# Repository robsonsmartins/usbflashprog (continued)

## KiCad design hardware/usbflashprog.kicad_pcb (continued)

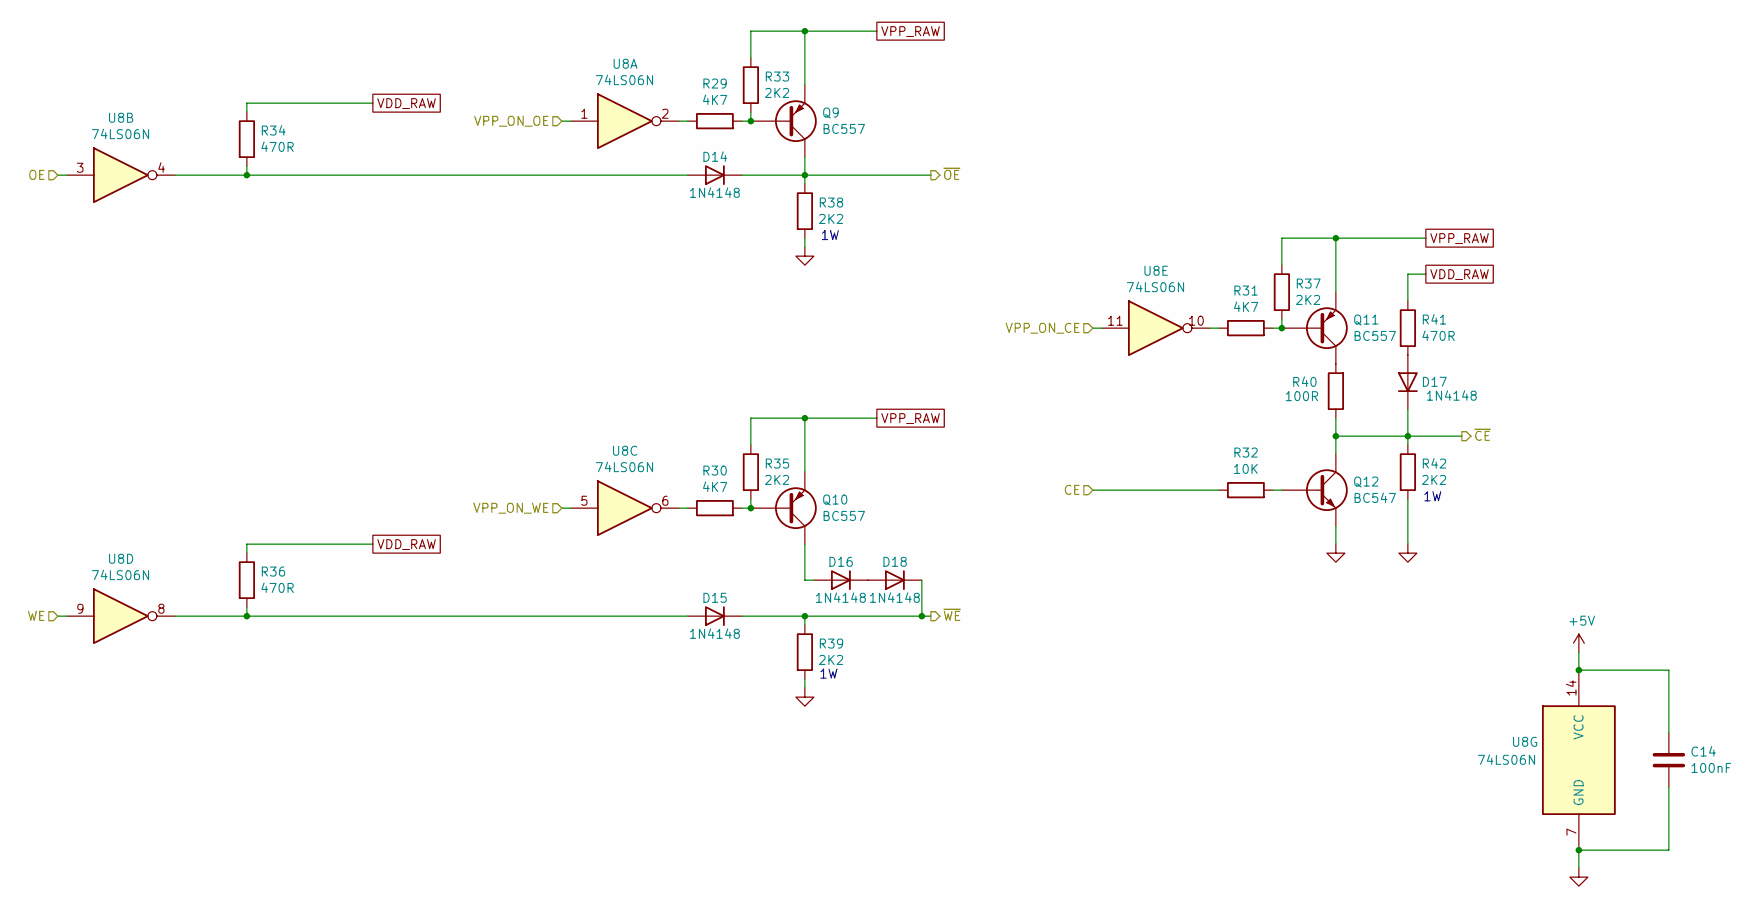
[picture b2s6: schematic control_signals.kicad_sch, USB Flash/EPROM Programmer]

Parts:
C14: 100nF; C_Disc_D5.0mm_W2.5mm_P5.00mm
D14, D15, D16, D17, D18: 1N4148; D_DO-34_SOD68_P7.62mm_Horizontal
Q9, Q10, Q11: BC557; TO-92_Inline_Wide
Q12: BC547; TO-92_Inline_Wide
R29, R30, R31: 4K7; R_Axial_DIN0204_L3.6mm_D1.6mm_P7.62mm_Horizontal
R32: 10K; R_Axial_DIN0204_L3.6mm_D1.6mm_P7.62mm_Horizontal
R33, R35, R37, R38, R39, R42: 2K2; R_Axial_DIN0204_L3.6mm_D1.6mm_P7.62mm_Horizontal
R34, R36, R41: 470R; R_Axial_DIN0204_L3.6mm_D1.6mm_P7.62mm_Horizontal
R40: 100R; R_Axial_DIN0204_L3.6mm_D1.6mm_P7.62mm_Horizontal
U8: 74LS06N; DIP-14_W7.62mm

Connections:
+5V: C14.1, U8.14 (VCC); also elsewhere on the board
/CPU/CE: R32.1; also elsewhere on the board
/CPU/OE: U8.3; also elsewhere on the board
/CPU/VPP_ON_CE: U8.11; also elsewhere on the board
/CPU/VPP_ON_OE: U8.1; also elsewhere on the board
/CPU/VPP_ON_WE: U8.5; also elsewhere on the board
/CPU/WE: U8.9; also elsewhere on the board
/~CE: D17.1 (K), Q12.1 (C), R40.1, R42.1; also elsewhere on the board
/~OE: D14.1 (K), Q9.1 (C), R38.1; also elsewhere on the board
/~WE: D15.1 (K), D18.1 (K), R39.1; also elsewhere on the board
GND: C14.2, Q12.3 (E), R38.2, R39.2, R42.2, U8.7 (GND); also elsewhere on the board
unnamed: D14.2 (A), R34.2, U8.4
unnamed: D15.2 (A), R36.2, U8.8
unnamed: D16.2 (A), Q10.1 (C)
unnamed: D16.1 (K), D18.2 (A)
unnamed: D17.2 (A), R41.2
unnamed: Q9.2 (B), R29.2, R33.2
unnamed: Q10.2 (B), R30.2, R35.2
unnamed: Q11.2 (B), R31.2, R37.2
unnamed: Q11.1 (C), R40.2
unnamed: Q12.2 (B), R32.2
unnamed: R29.1, U8.2
unnamed: R30.1, U8.6
unnamed: R31.1, U8.10
VDD_RAW: R34.1, R36.1, R41.1; also elsewhere on the board
VPP_RAW: Q9.3 (E), Q10.3 (E), Q11.3 (E), R33.1, R35.1, R37.1; also elsewhere on the board

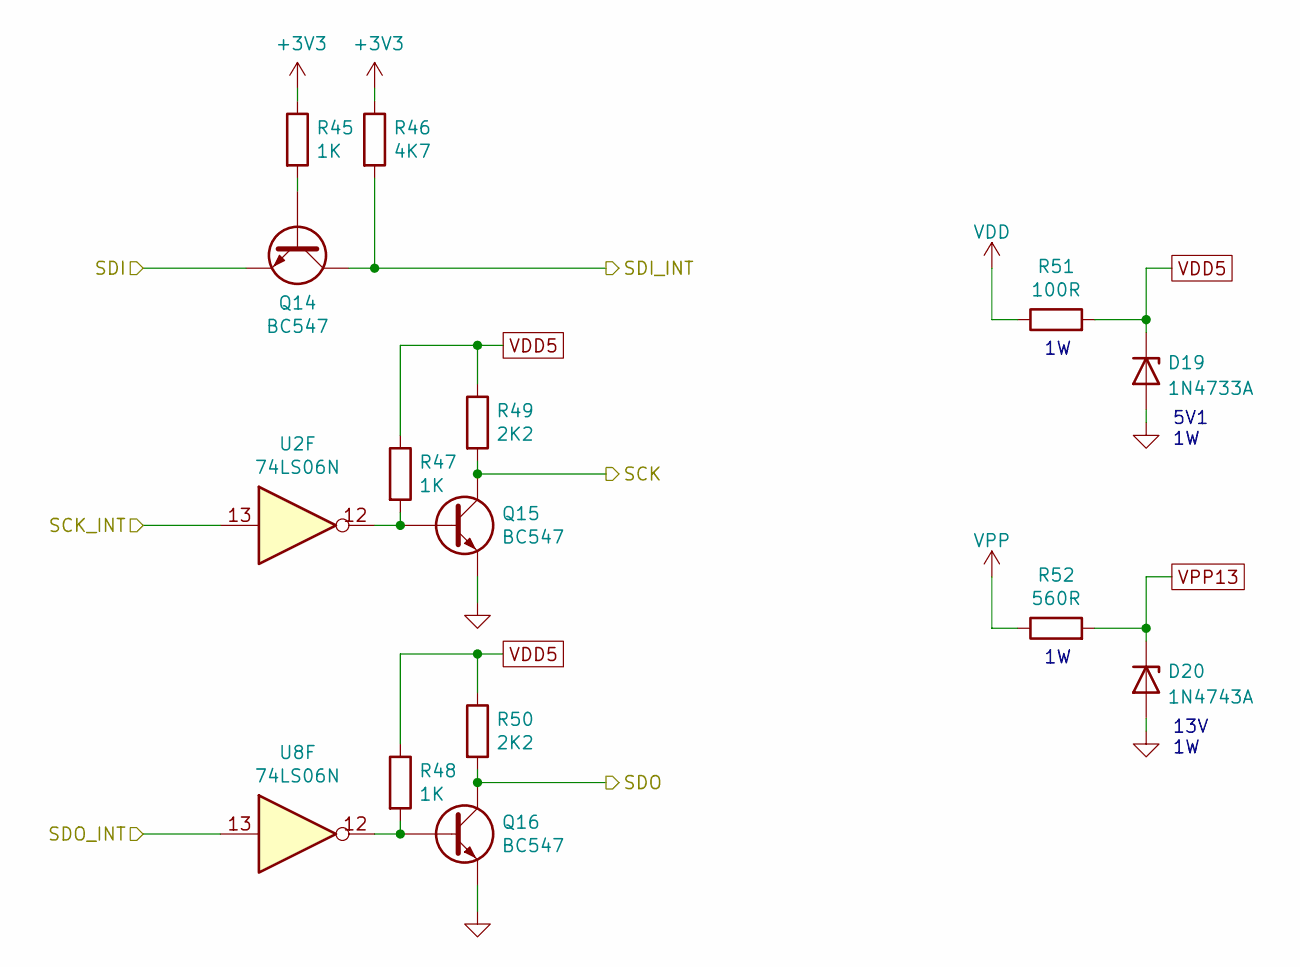
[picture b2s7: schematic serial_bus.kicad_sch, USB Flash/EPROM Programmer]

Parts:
D19: 1N4733A; D_DO-35_SOD27_P7.62mm_Horizontal
D20: 1N4743A; D_DO-35_SOD27_P7.62mm_Horizontal
Q14, Q15, Q16: BC547; TO-92_Inline_Wide
R45, R47, R48: 1K; R_Axial_DIN0204_L3.6mm_D1.6mm_P7.62mm_Horizontal
R46: 4K7; R_Axial_DIN0204_L3.6mm_D1.6mm_P7.62mm_Horizontal
R49, R50: 2K2; R_Axial_DIN0204_L3.6mm_D1.6mm_P7.62mm_Horizontal
R51: 100R; R_Axial_DIN0204_L3.6mm_D1.6mm_P7.62mm_Horizontal
R52: 560R; R_Axial_DIN0207_L6.3mm_D2.5mm_P10.16mm_Horizontal
U2, U8: 74LS06N; DIP-14_W7.62mm

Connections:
+3V3: R45.1, R46.1; also elsewhere on the board
/CPU/SCK_INT: U2.13; also elsewhere on the board
/CPU/SDI_INT: Q14.1 (C), R46.2; also elsewhere on the board
/CPU/SDO_INT: U8.13; also elsewhere on the board
/SCK: Q15.1 (C), R49.2; also elsewhere on the board
/SDI: Q14.3 (E); also elsewhere on the board
/SDO: Q16.1 (C), R50.2; also elsewhere on the board
GND: D19.2 (A), D20.2 (A), Q15.3 (E), Q16.3 (E); also elsewhere on the board
unnamed: Q14.2 (B), R45.2
unnamed: Q15.2 (B), R47.2, U2.12
unnamed: Q16.2 (B), R48.2, U8.12
VDD: R51.1; also elsewhere on the board
VDD5: D19.1 (K), R47.1, R48.1, R49.1, R50.1, R51.2; also elsewhere on the board
VPP: R52.1; also elsewhere on the board
VPP13: D20.1 (K), R52.2; also elsewhere on the board

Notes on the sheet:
13V 1W
5V1 1W

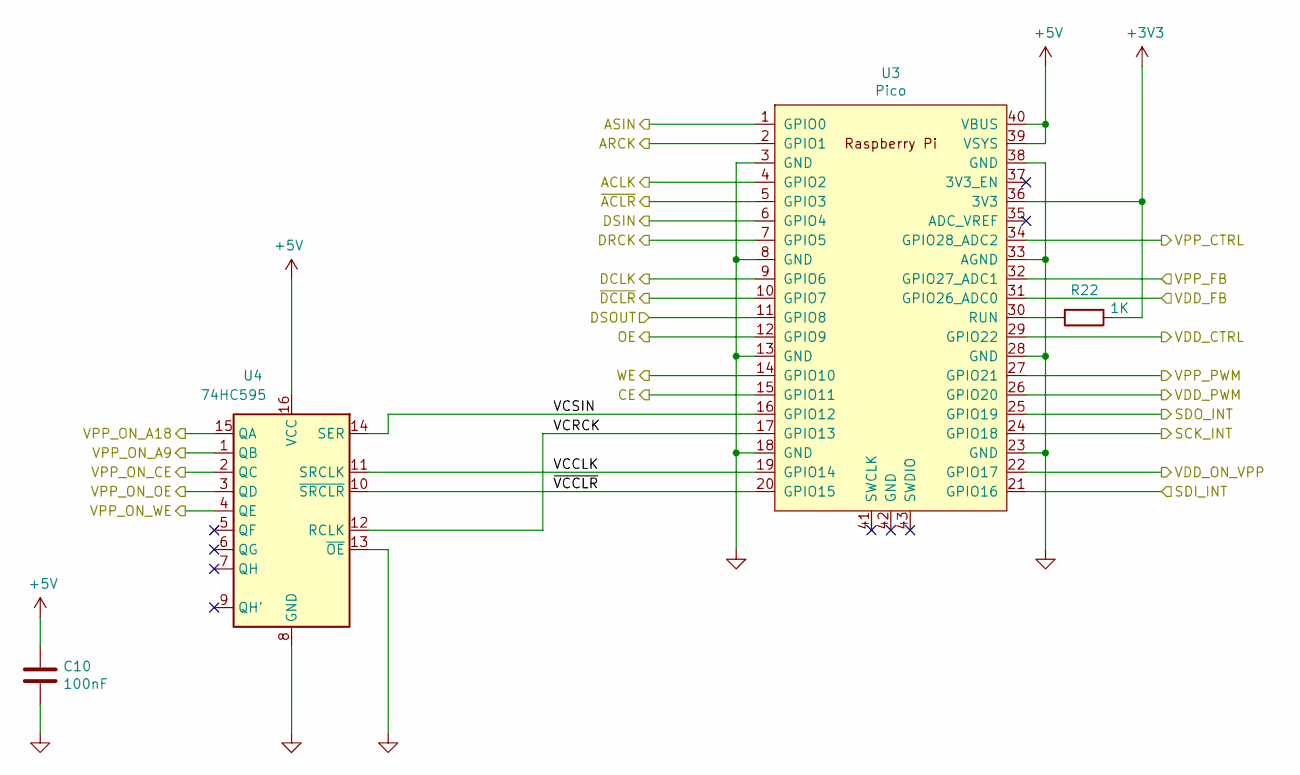
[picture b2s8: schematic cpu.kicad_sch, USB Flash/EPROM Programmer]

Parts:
C10: 100nF; C_Disc_D5.0mm_W2.5mm_P5.00mm
R22: 1K; R_Axial_DIN0204_L3.6mm_D1.6mm_P7.62mm_Horizontal
U3: Pico; RPi_Pico_SMD_TH
U4: 74HC595; DIP-16_W7.62mm

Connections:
+3V3: R22.1, U3.36 (3V3); also elsewhere on the board
+5V: C10.1, U3.39 (VSYS), U3.40 (VBUS), U4.16 (VCC); also elsewhere on the board
/Address Bus/ACLK: U3.4 (GPIO2); also elsewhere on the board
/Address Bus/ARCK: U3.2 (GPIO1); also elsewhere on the board
/Address Bus/ASIN: U3.1 (GPIO0); also elsewhere on the board
/Address Bus/VPP_ON_A9: U4.1 (QB); also elsewhere on the board
/Address Bus/VPP_ON_A18: U4.15 (QA); also elsewhere on the board
/Address Bus/~ACLR: U3.5 (GPIO3); also elsewhere on the board
/CPU/CE: U3.15 (GPIO11); also elsewhere on the board
/CPU/DCLK: U3.9 (GPIO6); also elsewhere on the board
/CPU/DRCK: U3.7 (GPIO5); also elsewhere on the board
/CPU/DSIN: U3.6 (GPIO4); also elsewhere on the board
/CPU/DSOUT: U3.11 (GPIO8); also elsewhere on the board
/CPU/OE: U3.12 (GPIO9); also elsewhere on the board
/CPU/SCK_INT: U3.24 (GPIO18); also elsewhere on the board
/CPU/SDI_INT: U3.21 (GPIO16); also elsewhere on the board
/CPU/SDO_INT: U3.25 (GPIO19); also elsewhere on the board
/CPU/VCCLK: U3.19 (GPIO14), U4.11 (SRCLK)
/CPU/VCRCK: U3.17 (GPIO13), U4.12 (RCLK)
/CPU/VCSIN: U3.16 (GPIO12), U4.14 (SER)
/CPU/VDD_CTRL: U3.29 (GPIO22); also elsewhere on the board
/CPU/VDD_FB: U3.31 (GPIO26_ADC0); also elsewhere on the board
/CPU/VDD_ON_VPP: U3.22 (GPIO17); also elsewhere on the board
/CPU/VDD_PWM: U3.26 (GPIO20); also elsewhere on the board
/CPU/VPP_CTRL: U3.34 (GPIO28_ADC2); also elsewhere on the board
/CPU/VPP_FB: U3.32 (GPIO27_ADC1); also elsewhere on the board
/CPU/VPP_ON_CE: U4.2 (QC); also elsewhere on the board
/CPU/VPP_ON_OE: U4.3 (QD); also elsewhere on the board
/CPU/VPP_ON_WE: U4.4 (QE); also elsewhere on the board
/CPU/VPP_PWM: U3.27 (GPIO21); also elsewhere on the board
/CPU/WE: U3.14 (GPIO10); also elsewhere on the board
/CPU/~DCLR: U3.10 (GPIO7); also elsewhere on the board
/CPU/~VCCLR: U3.20 (GPIO15), U4.10 (~SRCLR)
GND: C10.2, U3.3 (GND), U3.8 (GND), U3.13 (GND), U3.18 (GND), U3.23 (GND), U3.28 (GND), U3.33 (AGND), U3.38 (GND), U4.8 (GND), U4.13 (~OE); also elsewhere on the board
unnamed: R22.2, U3.30 (RUN)

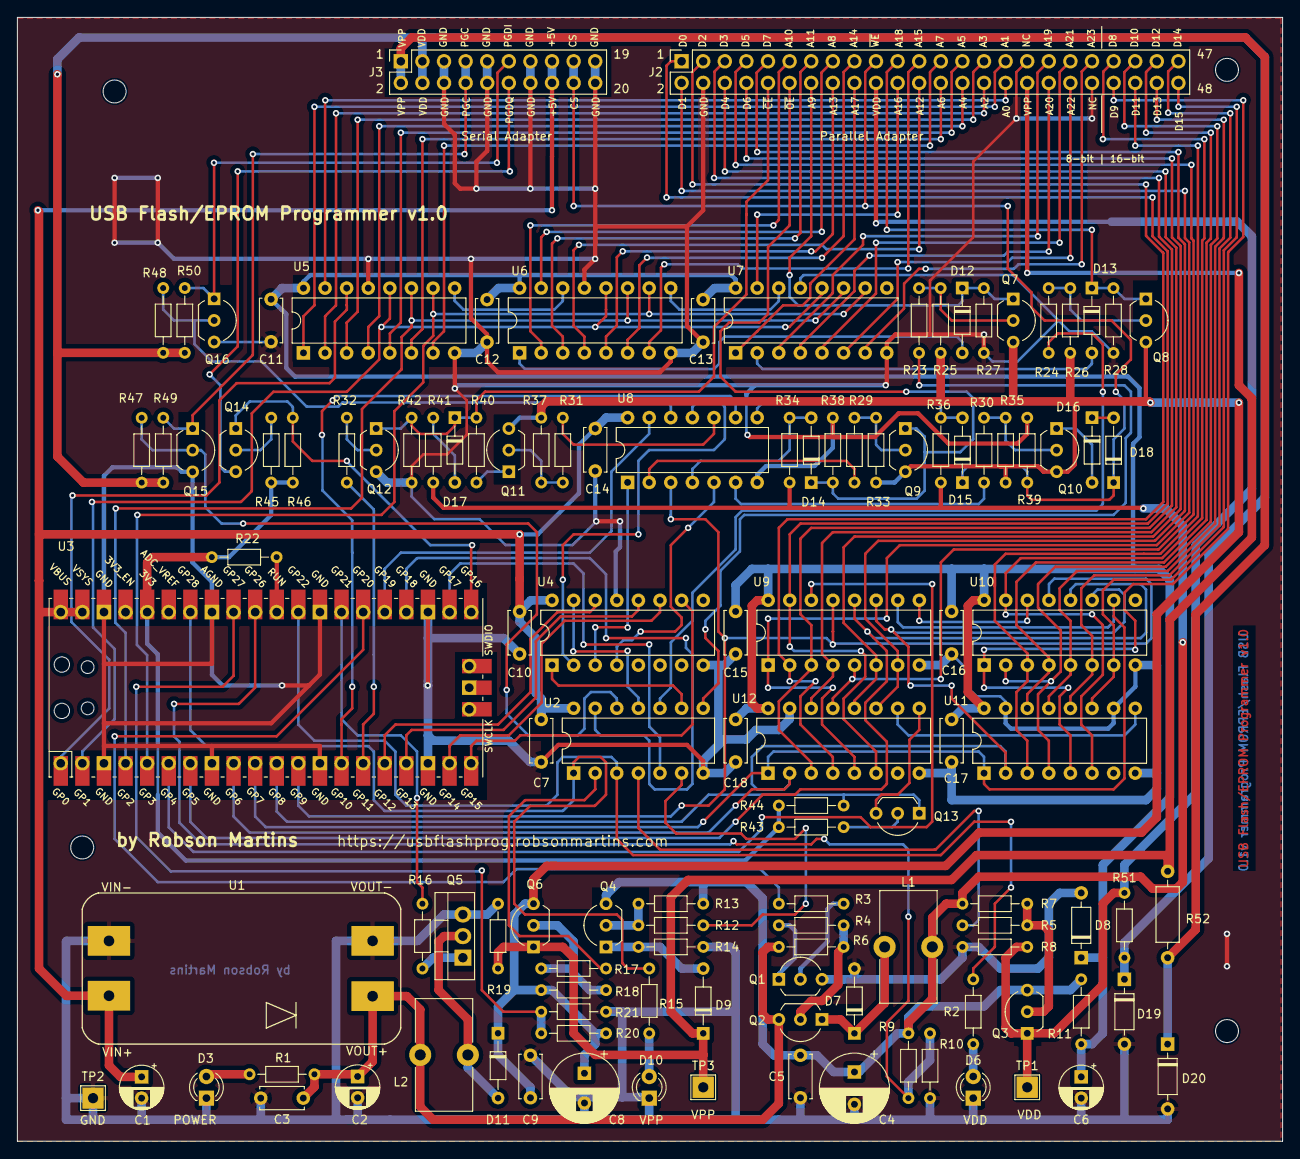
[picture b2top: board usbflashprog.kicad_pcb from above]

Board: 2 copper layers, 148.8 x 132.2 mm, 121 parts (0 on the bottom side), 133 nets.

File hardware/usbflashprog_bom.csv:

"Source:","E:\Users\Robson\Documentos\github-projects\usbflashprog\hardware\usbflashprog.kicad_sch"
"Date:","14/11/2023 17:15:45"
"Tool:","Eeschema 7.0.5"
"Generator:","C:\Program Files\KiCad\bin\scripting\plugins/bom_csv_grouped_by_value.py"
"Component Count:","121"

"Collated Components:"

"Item","Qty","Reference(s)","Value","LibPart","Footprint","Datasheet","DNP"
"1","2","C1, C2","10uF","Device:C_Polarized","Capacitor_THT:CP_Radial_D5.0mm_P2.50mm","~",""
"2","13","C3, C5, C7, C9, C10, C11, C12, C13, C14, C15, C16, C17, C18","100nF","Device:C","Capacitor_THT:C_Disc_D6.0mm_W2.5mm_P5.00mm","~",""
"3","1","C4","470uF","Device:C_Polarized","Capacitor_THT:CP_Radial_D8.0mm_P3.80mm","~",""
"4","1","C6","22uF","Device:C_Polarized","Capacitor_THT:CP_Radial_D5.0mm_P2.50mm","~",""
"5","1","C8","100uF","Device:C_Polarized","Capacitor_THT:CP_Radial_D8.0mm_P3.50mm","~",""
"6","1","D3","GREEN","Device:LED","LED_THT:LED_D3.0mm","~",""
"7","1","D6","RED","Device:LED","LED_THT:LED_D3.0mm","~",""
"8","2","D7, D11","BAT46","Diode:BAT46","Diode_THT:D_DO-35_SOD27_P7.62mm_Horizontal","http://www.vishay.com/docs/85662/bat46.pdf",""
"9","2","D8, D19","1N4733A","Diode:1N47xxA","Diode_THT:D_DO-41_SOD81_P10.16mm_Horizontal","https://www.vishay.com/docs/85816/1n4728a.pdf",""
"10","8","D9, D12, D13, D14, D15, D16, D17, D18","1N4148","Diode:1N4148","Diode_THT:D_DO-35_SOD27_P7.62mm_Horizontal","https://assets.nexperia.com/documents/data-sheet/1N4148_1N4448.pdf",""
"11","1","D10","YELLOW","Device:LED","LED_THT:LED_D3.0mm","~",""
"12","1","D20","1N4743A","Diode:1N47xxA","Diode_THT:D_DO-41_SOD81_P10.16mm_Horizontal","https://www.vishay.com/docs/85816/1n4728a.pdf",""
"13","1","J2","Parallel Adapter","Connector_Generic:Conn_02x24_Odd_Even","Connector_PinSocket_2.54mm:PinSocket_2x24_P2.54mm_Vertical","~",""
"14","1","J3","Serial Adapter","Connector_Generic:Conn_02x10_Odd_Even","Connector_PinSocket_2.54mm:PinSocket_2x10_P2.54mm_Vertical","~",""
"15","1","L1","100uH","Device:L_Ferrite","Inductor_THT:L_Toroid_Vertical_L13.0mm_W6.5mm_P5.60mm","~",""
"16","1","L2","300uH","Device:L_Ferrite","Inductor_THT:L_Toroid_Vertical_L13.0mm_W6.5mm_P5.60mm","~",""
"17","4","Q1, Q12, Q13, Q16","BC547","Transistor_BJT:BC547","Package_TO_SOT_THT:TO-92_Inline_Wide","https://www.onsemi.com/pub/Collateral/BC550-D.pdf",""
"18","1","Q2","BC327",":BC327_1","Package_TO_SOT_THT:TO-92_Inline_Wide","http://www.onsemi.com/pub_link/Collateral/BC327-D.PDF",""
"19","1","Q3","BC327",":BC327_2","Package_TO_SOT_THT:TO-92_Inline_Wide","http://www.onsemi.com/pub_link/Collateral/BC327-D.PDF",""
"20","2","Q4, Q6","BC327","Transistor_BJT:BC327","Package_TO_SOT_THT:TO-92_Inline_Wide","http://www.onsemi.com/pub_link/Collateral/BC327-D.PDF",""
"21","1","Q5","TIP120","Transistor_BJT:TIP120","Package_TO_SOT_THT:TO-220-3_Vertical","https://www.onsemi.com/pub/Collateral/TIP120-D.PDF",""
"22","2","Q7, Q9","BC557",":BC557_1","Package_TO_SOT_THT:TO-92_Inline_Wide","https://www.onsemi.com/pub/Collateral/BC556BTA-D.pdf",""
"23","2","Q8, Q11","BC557","Transistor_BJT:BC557","Package_TO_SOT_THT:TO-92_Inline_Wide","https://www.onsemi.com/pub/Collateral/BC556BTA-D.pdf",""
"24","1","Q10","BC557",":BC557_2","Package_TO_SOT_THT:TO-92_Inline_Wide","https://www.onsemi.com/pub/Collateral/BC556BTA-D.pdf",""
"25","1","Q14","BC547",":BC547_1","Package_TO_SOT_THT:TO-92_Inline_Wide","https://www.onsemi.com/pub/Collateral/BC550-D.pdf",""
"26","1","Q15","BC547",":BC547_2","Package_TO_SOT_THT:TO-92_Inline_Wide","https://www.onsemi.com/pub/Collateral/BC550-D.pdf",""
"27","19","R1, R5, R6, R7, R12, R13, R18, R25, R26, R27, R28, R33, R35, R37, R38, R39, R42, R49, R50","2K2","Device:R","Resistor_THT:R_Axial_DIN0207_L6.3mm_D2.5mm_P10.16mm_Horizontal","~",""
"28","5","R2, R11, R15, R40, R51","100R","Device:R","Resistor_THT:R_Axial_DIN0207_L6.3mm_D2.5mm_P10.16mm_Horizontal","~",""
"29","7","R3, R8, R22, R43, R45, R47, R48","1K","Device:R","Resistor_THT:R_Axial_DIN0207_L6.3mm_D2.5mm_P10.16mm_Horizontal","~",""
"30","10","R4, R17, R19, R23, R24, R29, R30, R31, R44, R46","4K7","Device:R","Resistor_THT:R_Axial_DIN0207_L6.3mm_D2.5mm_P10.16mm_Horizontal","~",""
"31","5","R9, R21, R34, R36, R41","470R","Device:R","Resistor_THT:R_Axial_DIN0207_L6.3mm_D2.5mm_P10.16mm_Horizontal","~",""
"32","1","R10","330R","Device:R","Resistor_THT:R_Axial_DIN0207_L6.3mm_D2.5mm_P10.16mm_Horizontal","~",""
"33","2","R14, R32","10K","Device:R","Resistor_THT:R_Axial_DIN0207_L6.3mm_D2.5mm_P10.16mm_Horizontal","~",""
"34","1","R16","220R","Device:R","Resistor_THT:R_Axial_DIN0207_L6.3mm_D2.5mm_P10.16mm_Horizontal","~",""
"35","1","R20","3K9","Device:R","Resistor_THT:R_Axial_DIN0207_L6.3mm_D2.5mm_P10.16mm_Horizontal","~",""
"36","1","R52","560R","Device:R","Resistor_THT:R_Axial_DIN0309_L9.0mm_D3.2mm_P15.24mm_Horizontal","~",""
"37","1","TP1","VDD","Connector:TestPoint","TestPoint:TestPoint_THTPad_2.5x2.5mm_Drill1.2mm","~",""
"38","1","TP2","GND","Connector:TestPoint","TestPoint:TestPoint_THTPad_2.5x2.5mm_Drill1.2mm","~",""
"39","1","TP3","VPP","Connector:TestPoint","TestPoint:TestPoint_THTPad_2.5x2.5mm_Drill1.2mm","~",""
"40","1","U1","MT3608 Module","DC2DC_Modules:MT3608_Module","DC2DC_Modules:MT3608_module","https://support.envistiamall.com/kb/mt3608-2v-28v-micro-usb-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",""
"41","2","U2, U8","74LS06N","74xx:74LS06N","Package_DIP:DIP-14_W7.62mm","http://www.ti.com/lit/gpn/sn74LS06N",""
"42","1","U3","Pico","MCU_RaspberryPi_and_Boards:Pico","MCU_RaspberryPi_and_Boards:RPi_Pico_SMD_TH","",""
"43","6","U4, U5, U6, U7, U9, U10","74HC595","74xx:74HC595","Package_DIP:DIP-16_W7.62mm","http://www.ti.com/lit/ds/symlink/sn74hc595.pdf",""
"44","2","U11, U12","74HC165","74xx:74HC165","Package_DIP:DIP-16_W7.62mm","https://assets.nexperia.com/documents/data-sheet/74HC_HCT165.pdf",""

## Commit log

2022-04-19 Initial commit (migrated from sourceforge.net).
2022-04-23 Rev.E. CPU changed to Raspberry Pi Pico. Updated diagrams. Removed PT_BR translation.
2022-04-25 Rev.E. Updated project site.
2022-04-25 Rev.E. Initial hardware design.
2022-04-26 Rev.E. Update Readme. Add LibreOffice lock files to gitignore.
2022-04-27 Rev.E. Updated hardware design.
2022-04-27 Rev.E. Add readme to doc directory.
2022-04-28 Rev.E. Updated specifications document and hardware design.
2022-04-28 Rev.E. Updated readme and hardware BOM.
2022-04-30 Rev.E. Updated R51 wattage.
2022-05-03 Rev.E. Add Initial Firmware Project and documentation.
2022-05-03 Rev.E. Created github-pages documentation
2022-05-04 Rev.E. Created github-pages documentation.
2022-05-04 Rev.E. Updated documentation.
2022-05-04 Rev.E. Update readme.
2022-05-04 Rev.E. Update index.md
2022-05-04 Rev.E. Added UT's for firmware project.
2022-05-07 Rev.E. Add ADC class and UT.
2022-05-08 Rev.E. Updated documentation. Added code coverage report.
2022-05-08 Rev.E. Updated cmake scripts. Updated documentation.
2022-05-08 Rev.E. Updated CI/CD script.
2022-05-08 Rev.E. Updated pulse time test tolerance.
2022-05-08 Rev.E. Updated CI/CD code analysis.
2022-05-09 Rev.E. Created PWM Class. Updated documentation.
2022-05-09 Rev.E. Add tests for PWM Class.
2022-05-09 Rev.E. Update codeql analysis script.
2022-05-09 Rev.E. Create initial security policy file.
2022-05-10 Rev.E. Add MultiCore HAL class and UT.
2022-05-12 Rev.E. Add DC2DC circuits class and UT. Revised all code and doxygen docs.
2022-05-15 Rev.E. Add Dc2Dc Converter and Voltage Generator classes.
2022-05-16 Rev.E. Add UT for VGenerator and revised Dc2Dc, Pwm and VGenerator classes.
2022-05-16 Rev.E. Add Test Points for VDD/VPP/GND.
2022-05-19 DRAFT. Proposal with Boost Converter to eliminate external power supply.
2022-05-23 Rev.E. Add flash space class and UT. Updated VGenerator.
2022-05-25 Rev.E. Update VGenerator class and UT. Update README. Update docs.
2022-05-25 Rev.E. Update README
2022-05-25 Rev.E. Update docs
2022-05-25 Rev.E. Update VGenerator and UT.
2022-05-29 Rev.E. Add string, serial and runner classes
2022-05-29 Rev.E. Update classes
2022-05-29 Rev.E. Update documentation
2022-05-31 Rev.E. Update String, Serial and Runner classes
2022-05-31 Rev.E. Add UT's for Serial and String classes
2022-05-31 Rev.E. Update firmware documentation
2022-06-02 Rev.F. Updated schematics
2022-06-02 Rev.F. Added codes/commands for communication
2022-06-02 Rev.F. Initial software project
2022-06-02 Rev.F. Updated documentation
2022-06-02 Rev.F. Ignore backup files from Kicad.
2022-06-02 Rev.F Update CMake directives for ts compilation
2022-06-03 Rev.F. Update README. Add BUILD instructions
2022-06-03 Rev.F. Ignore backups from Kicad
2022-06-03 Rev.F. Update BUILD instructions
2022-06-05 Rev.F. Updated software project and documentation
2022-06-06 Rev.F. Updated software project
2022-06-06 Rev.F. Initial version
2022-06-06 Rev.F. Removed travis support
2022-06-08 Rev.F. Update github action scripts
2022-06-09 Rev.F. Update documentation
2022-06-09 Rev.F. Add DEB package system
2022-06-11 Rev.F. Update Firmware project
2022-06-12 Rev.F. Update Software project
2022-06-25 Rev.F. Update build scripts
2022-06-30 Rev.F. Add support to build on macos
2022-07-06 Rev.F. Update project
2022-07-07 Rev.F. Add support to Qt < 5.10
2022-07-10 Rev.F. Remove warnings
2022-07-10 Rev.F. Add support to FreeBSD
2022-07-14 Rev.F. Update GUI
2022-07-14 Rev.F. Add Unit Tests
2022-08-17 Rev.F. Add CDC driver to Windows 7
2022-08-18 Rev.F. Add basic hex editor
2022-08-24 Rev.F. Update hex editor and software project
2022-08-30 simulator: Initial commit
2022-08-30 simulator: iowrapper
2022-09-01 simulator: prog, chip, emuprog gui, install-script
2022-09-13 simulator: update emuprog gui
2022-09-15 Rev.F. Update workflow for build software
2022-09-29 Rev.F. Firmware - add data and address bus support
2022-09-29 Rev.F. Update firmware documentation
2022-09-29 Rev.F. Software - add data and address bus support
2022-09-29 Rev.F. Update software documentation
2023-10-20 Rev.F. Update software and firmware build docs
    Committer: Robson Martins <robsonsmartins@gmail.com>
2023-10-21 Rev.G. Update README
2023-11-14 Rev.G. Change external power supply to a MT3606 DC-DC Module
2023-11-17 Rev.G. Update specs
2023-11-17 Rev.G. Fix type errors in backend/opcodes
2023-11-21 Rev.G. Fix Build Software Action errors
2023-11-21 Rev.G. Fix compilation warnings under macos
2023-11-29 Rev.G. Update software backend/runner
2023-11-29 Rev.G. Update software tests
2023-12-13 simulator: fix cross dll generation under linux
2023-12-13 simulator: add the code documentation
2023-12-13 simulator: fix 32-bit executables calls
2023-12-13 simulator: add code formater
2023-12-13 Rev.G. Update software documentation
2023-12-13 Rev.G. Update software coverage, build and test scripts
2023-12-13 Rev.G. Update software coverage documentation
2023-12-13 Rev.G. Update firmware documentation
2023-12-13 Rev.G. Update firmware coverage documentation
2023-12-13 Rev.G. Update firmware coverage, build and test scripts
2023-12-13 Rev.G. Update software source format. Add base device and actions. Update ui.
2023-12-13 Rev.G. Fix cmake 3.0 deprecation in third party
2023-12-18 Rev.G. Add software prog actions and devices
2023-12-18 Rev.G. Add script to update language tokens
2023-12-19 Rev.G. Add SRAM device and update documentation
2023-12-22 Rev.G. Improve the hexeditor
2023-12-23 0.2.rev.A. Update version and readme
2023-12-23 0.2.rev.A. Enable VDD and VPP control in software
2023-12-23 0.2.rev.A. Add EPROM 27xxx device
2023-12-26 0.2.rev.A. Separate VDD read/prog control and Add size selector in software
2024-01-02 0.2.rev.A. UI improvements in software; Add EPROM 27/27C device
2024-01-02 0.2.rev.A. Fix deprecated message when test firmware
2024-01-02 0.2.rev.A. Update github action scripts
2024-01-02 0.2.rev.A. Update version information in documentation
2024-01-02 Update Firmware Documentation
2024-01-02 Update Software Documentation
2024-01-03 0.2.rev.A. Add VEE control in software; Add Erasable EPROM devices
2024-01-04 simulator: add button to open log file
2024-01-04 simulator: fix log timestamp
2024-01-04 simulator: fix SetSize order
2024-01-05 0.2.rev.A. Fix SRAM and EPROM errors
2024-01-05 0.2.rev.A. Add tests to devices
2024-01-05 0.2.rev.A. Fix delay test errors
2024-01-05 simulator: add eprom erase feature
2024-01-05 0.2.rev.A. Increasing test coverage
2024-01-05 0.2.rev.A. Fix coverage lcov params
2024-01-08 0.2.rev.A. Fix increment address and bit methods (bus) in firmware
2024-01-08 0.2.rev.A. Fix vgenerator init and vget() in firmware
2024-01-08 0.2.rev.A. Update firmware source formatter
2024-01-08 0.2.rev.A. Update SRAM test algorithm
2024-01-08 0.2.rev.A. Improve software Runner:msDelay()
2024-01-08 0.2.rev.A. Improve software UI progress and calibration dialogs
2024-01-09 0.2.rev.A. Fix serial communication in firmware
2024-01-12 0.2.rev.A. Fix serial communication; Add logger; UI improvements; Add settings dialog
2024-01-12 0.2.rev.A. Fix shift and clear logic of 74hc595 in firmware
2024-01-14 0.2.rev.A. Add new comm opcodes (firmware and software) for device programming
2024-01-14 0.2.rev.A. UI improvements in software
2024-01-14 0.2.rev.A. Update device manufacturer codes (getid)
2024-01-17 0.2.rev.A. Update README
2024-01-18 0.2.rev.A. Add Get ID support check routine in firmware
2024-01-19 0.2.rev.A. Fix calibration process
2024-01-19 0.2.rev.A. Add icons license file
2024-01-25 0.2.rev.A. Add reference/datasheets
2024-01-25 0.2.rev.A. Fix program routine
2024-01-26 0.2.rev.A. Add EzoFlash+ cross adapter (initial version)
2024-02-02 0.2.rev.A. Add new comm opcodes; UI improvements; Add EEPROM support
2024-02-02 0.2.rev.A. Fix github actions warnings
2024-02-02 0.3. Update version
2024-02-02 0.3.rev.A. Enable protect action in dummy device
2024-02-03 simulator: add eeprom28c sector prog and protect/unprotect features
2024-02-03 0.3.rev.A. Improve EEPROM support
2024-02-13 0.3.rev.A. Improve communication device opcodes
2024-02-24 simulator: add flash28f, flash i28f, flash i28f-16bit support; refactor to use new integer types
2024-02-24 simulator: add documentation, license and references
2024-02-24 simulator: add github actions workflow
2024-02-24 0.3.rev.A. Add Flash28F support
2024-02-24 0.3.rev.A. Update references/datasheets
2024-02-28 0.3.rev.A. Update documentation
2024-03-08 0.3.rev.A. Add/Update kicad libraries
2024-03-14 0.3.rev.A. Created new main pcb
2024-03-14 0.3.rev.A. Updated adapters/ezoflash cross adapter
